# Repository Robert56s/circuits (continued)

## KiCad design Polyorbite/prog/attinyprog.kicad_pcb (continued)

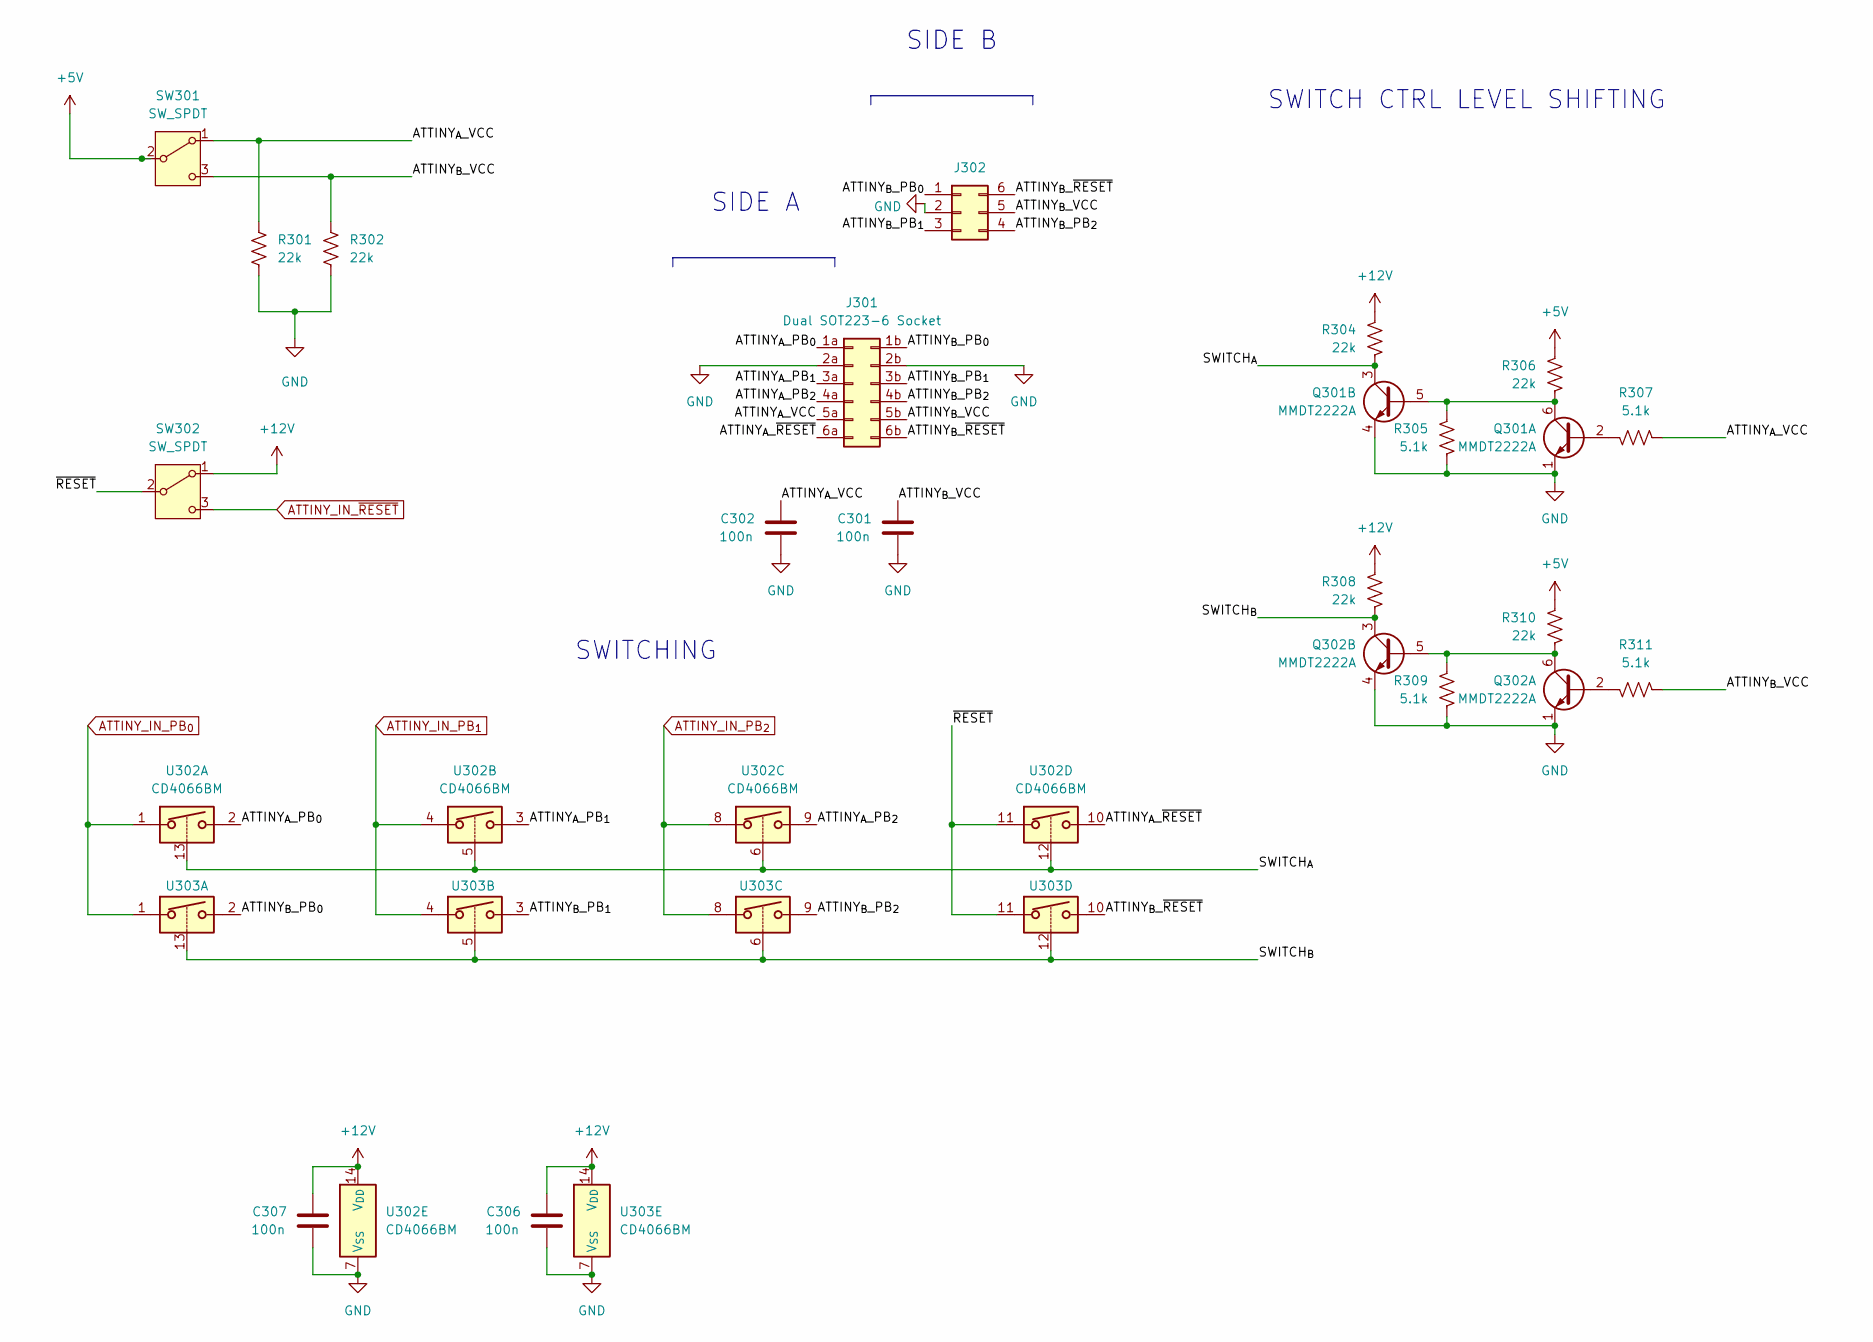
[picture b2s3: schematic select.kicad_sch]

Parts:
C301, C302, C306, C307: 100n; C_0402_1005Metric
J301: Dual SOT223-6 Socket; SOT223-6_Double_Socket
J302: Conn_02x03_Counter_Clockwise; PinHeader_2x03_P2.54mm_Vertical
Q301, Q302: MMDT2222A; SOT-363_SC-70-6
R301, R302, R304, R306, R308, R310: 22k; R_0402_1005Metric
R305, R307, R309, R311: 5.1k; R_0402_1005Metric
SW301, SW302: SW_SPDT; SW_SPDT_PCM12
U302, U303: CD4066BM; SO-14_3.9x8.65mm_P1.27mm

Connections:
+5V: R306.1, R310.1, SW301.2 (B); also elsewhere on the board
+12V: C306.1, C307.1, R304.1, R308.1, SW302.1 (A), U302.14 (V_{DD}), U303.14 (V_{DD}); also elsewhere on the board
/socket and selectors/ATTINY_{A}_PB_{0}: J301.1a, U302.2
/socket and selectors/ATTINY_{A}_PB_{1}: J301.3a, U302.3
/socket and selectors/ATTINY_{A}_PB_{2}: J301.4a, U302.9
/socket and selectors/ATTINY_{A}_VCC: C302.1, J301.5a, R301.1, R307.1, SW301.1 (A)
/socket and selectors/ATTINY_{A}_~RESET: J301.6a, U302.10
/socket and selectors/ATTINY_{B}_PB_{0}: J301.1b, J302.1, U303.2
/socket and selectors/ATTINY_{B}_PB_{1}: J301.3b, J302.3, U303.3
/socket and selectors/ATTINY_{B}_PB_{2}: J301.4b, J302.4, U303.9
/socket and selectors/ATTINY_{B}_VCC: C301.1, J301.5b, J302.5, R302.1, R311.1, SW301.3 (C)
/socket and selectors/ATTINY_{B}_~RESET: J301.6b, J302.6, U303.10
/socket and selectors/SWITCH_{A}: Q301.3 (C2), R304.2, U302.5, U302.6, U302.12, U302.13
/socket and selectors/SWITCH_{B}: Q302.3 (C2), R308.2, U303.5, U303.6, U303.12, U303.13
/socket and selectors/~RESET: SW302.2 (B), U302.11, U303.11
ATTINY_IN_PB_{0}: U302.1, U303.1; also elsewhere on the board
ATTINY_IN_PB_{1}: U302.4, U303.4; also elsewhere on the board
ATTINY_IN_PB_{2}: U302.8, U303.8
ATTINY_IN_~RESET: SW302.3 (C); also elsewhere on the board
GND: C301.2, C302.2, C306.2, C307.2, J301.2a, J301.2b, J302.2, Q301.1 (E1), Q301.4 (E2), Q302.1 (E1), Q302.4 (E2), R301.2, R302.2, R305.1, R309.1, U302.7 (V_{SS}), U303.7 (V_{SS}); also elsewhere on the board
unnamed: Q301.2 (B1), R307.2
unnamed: Q301.5 (B2), Q301.6 (C1), R305.2, R306.2
unnamed: Q302.2 (B1), R311.2
unnamed: Q302.5 (B2), Q302.6 (C1), R309.2, R310.2

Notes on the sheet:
SWITCH CTRL LEVEL SHIFTING
SIDE A
SWITCHING
SIDE B

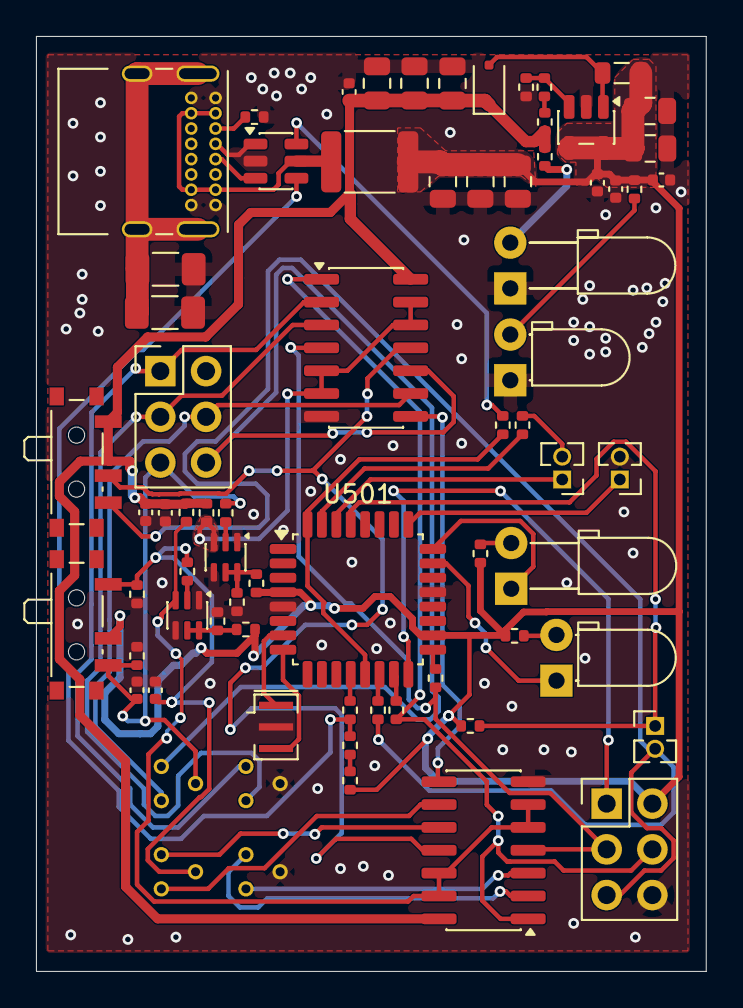
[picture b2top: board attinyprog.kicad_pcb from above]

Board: 2 copper layers, 37.2 x 51.9 mm, 69 parts (1 on the bottom side), 54 nets.

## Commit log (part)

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2025-11-03 circuit
2025-11-04 current
2025-11-07 fixed tp4
2025-11-07 cours8
2025-11-12 blabla
2025-11-13 update test arduino
2025-11-14 fuck you
2025-11-19 good
2025-11-19 push
